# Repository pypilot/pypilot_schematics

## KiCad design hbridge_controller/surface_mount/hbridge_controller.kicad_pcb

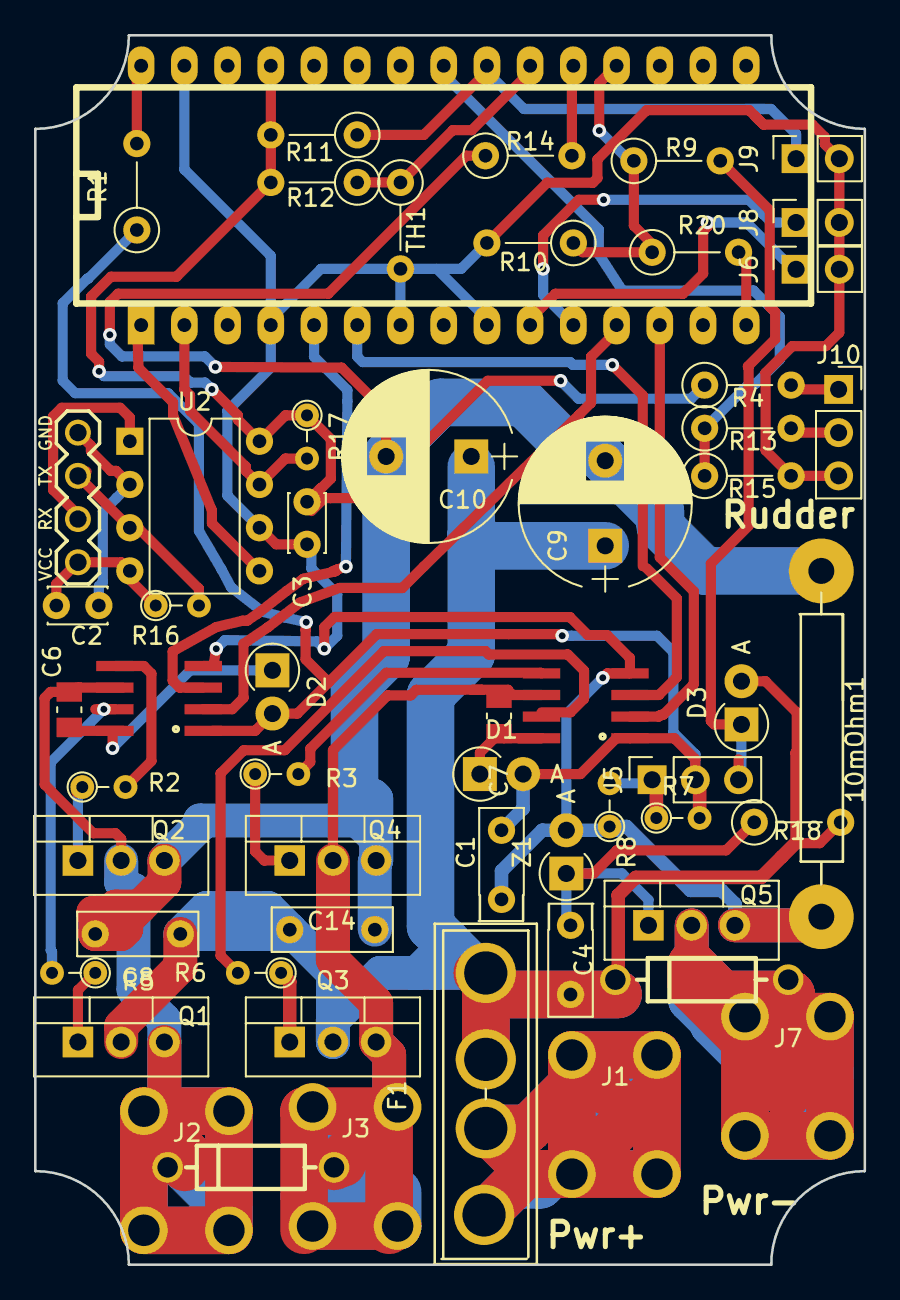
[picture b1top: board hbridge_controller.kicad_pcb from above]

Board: 2 copper layers, 48.8 x 72.2 mm, 57 parts (0 on the bottom side), 43 nets.

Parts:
10mOhm1: R; Resistor_Horizontal_RM10mm
A1: Arduino_Nano_v3.x; arduino_mini
C1, C4: 4.7uF; C_Disc_D5.0mm_W2.5mm_P2.50mm
C2, C3: .1uF; C_Disc_D3.4mm_W2.1mm_P2.50mm
C6, C7: .22uF; C_0805_2012Metric_Pad1.15x1.50mm_HandSolder
C8, C14: 4.7uF; C_Disc_D7.0mm_W2.5mm_P5.00mm
C9, C10: 330uF; CP_Radial_D10.0mm_P5.00mm
D1, D2, D3: 1N4001; D_T-1_P2.54mm_Vertical_AnodeUp
F1: FUSE; BladeFuse-CarType
J1: Pwr+; screw_terminal
J2: Motor A; screw_terminal
J3: Motor B; screw_terminal
J4: UART_Device; uart
J5: 12v REG/R; PinSocket_1x03_P2.54mm_Vertical
J6, J8, J9: Conn_01x02; PinSocket_1x02_P2.54mm_Vertical
J7: Pwr-; screw_terminal
J10: SENSE; PinSocket_1x03_P2.54mm_Vertical
Q1, Q2, Q3, Q4, Q5: Q_NMOS_GDS; TO-220-3_Vertical
R1: 100; R_Axial_DIN0207_L6.3mm_D2.5mm_P5.08mm_Vertical
R2, R3, R5, R6: 47; R_Axial_DIN0204_L3.6mm_D1.6mm_P2.54mm_Vertical
R4: 200; R_Axial_DIN0207_L6.3mm_D2.5mm_P5.08mm_Vertical
R7: 3900; R_Axial_DIN0204_L3.6mm_D1.6mm_P2.54mm_Vertical
R8: 560; R_Axial_DIN0204_L3.6mm_D1.6mm_P2.54mm_Vertical
R9, R18: 10k; R_Axial_DIN0207_L6.3mm_D2.5mm_P5.08mm_Vertical
R10, R14, R20: 560; R_Axial_DIN0207_L6.3mm_D2.5mm_P5.08mm_Vertical
R11, R12, R13: 100k; R_Axial_DIN0207_L6.3mm_D2.5mm_P5.08mm_Vertical
R15: 20k; R_Axial_DIN0207_L6.3mm_D2.5mm_P5.08mm_Vertical
R16, R17: 2.4k; R_Axial_DIN0204_L3.6mm_D1.6mm_P2.54mm_Vertical
TH1: Thermistor; R_Axial_DIN0207_L6.3mm_D2.5mm_P5.08mm_Vertical
TVS1: TVS; tvs
TVS2: TVS; DIODE-1N4001
U1, U3: NCP5106B; SO08_4mm
U2: cpc5001; DIP-8_W7.62mm
Z1: 10v; D_T-1_P2.54mm_Vertical_AnodeUp

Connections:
+5V: A1.27, C3.1, R4.1, R11.2, R12.2, R17.1, U2.8
+12V: C1.1, D1.2, D2.2, J5.2, R1.1, R7.2, U1.1, U3.1
/sense/PWMAH: A1.12, U1.2
/sense/PWMAL: A1.5, U1.3
/sense/PWMBH: A1.13, U3.2
/sense/PWMBL: A1.6, U3.3
/sense/Power: D3.1, J5.3, R9.2
/sense/Shunt: 10mOhm1.1, C8.2, C9.2, C10.2, C14.2, Q2.3, Q4.3, R14.1
GND: 10mOhm1.2, A1.4, A1.7, A1.9, A1.29, C1.2, C3.2, J6.2, J8.2, J9.2, J10.3, Q5.3, R8.1, R10.2, R15.2, TH1.2, U1.4, U2.6, U3.4, Z1.2
unnamed: A1.1, U2.5
unnamed: A1.2, R17.2, U2.7
unnamed: A1.10, J6.1
unnamed: A1.11, J8.1
unnamed: A1.15, R20.2
unnamed: A1.19, R9.1, R10.1, R20.1
unnamed: A1.20, R14.2
unnamed: A1.21, R12.1, TH1.1
unnamed: A1.22, J9.1, R11.1
unnamed: A1.23, R13.1, R15.1
unnamed: A1.30, R1.2
unnamed: C2.1, J4.1, R16.1, U2.4
unnamed: C2.2, J4.4, U2.2
unnamed: C4.2, Q5.1, R18.1, Z1.1
unnamed: C6.1, D2.1, U1.8
unnamed: C6.2, J2.1, Q1.3, Q2.2, TVS1.K, U1.6
unnamed: C7.1, D1.1, U3.8
unnamed: C7.2, J3.1, Q3.3, Q4.2, TVS1.A, U3.6
unnamed: F1.1, J1.1
unnamed: J4.2, U2.1
unnamed: J4.3, R16.2, U2.3
unnamed: J5.1, R7.1, R8.2
unnamed: J7.1, Q5.2, TVS2.A
unnamed: J10.1, R4.2
unnamed: J10.2, R13.2
unnamed: Q1.1, R5.1
unnamed: Q2.1, R2.1
unnamed: Q3.1, R6.1
unnamed: Q4.1, R3.1
unnamed: R2.2, U1.5
unnamed: R3.2, U3.5
unnamed: R5.2, U1.7
unnamed: R6.2, U3.7
VCC: C4.1, C8.1, C9.1, C10.1, C14.1, D3.2, F1.2, Q1.2, Q3.2, R18.2, TVS2.K

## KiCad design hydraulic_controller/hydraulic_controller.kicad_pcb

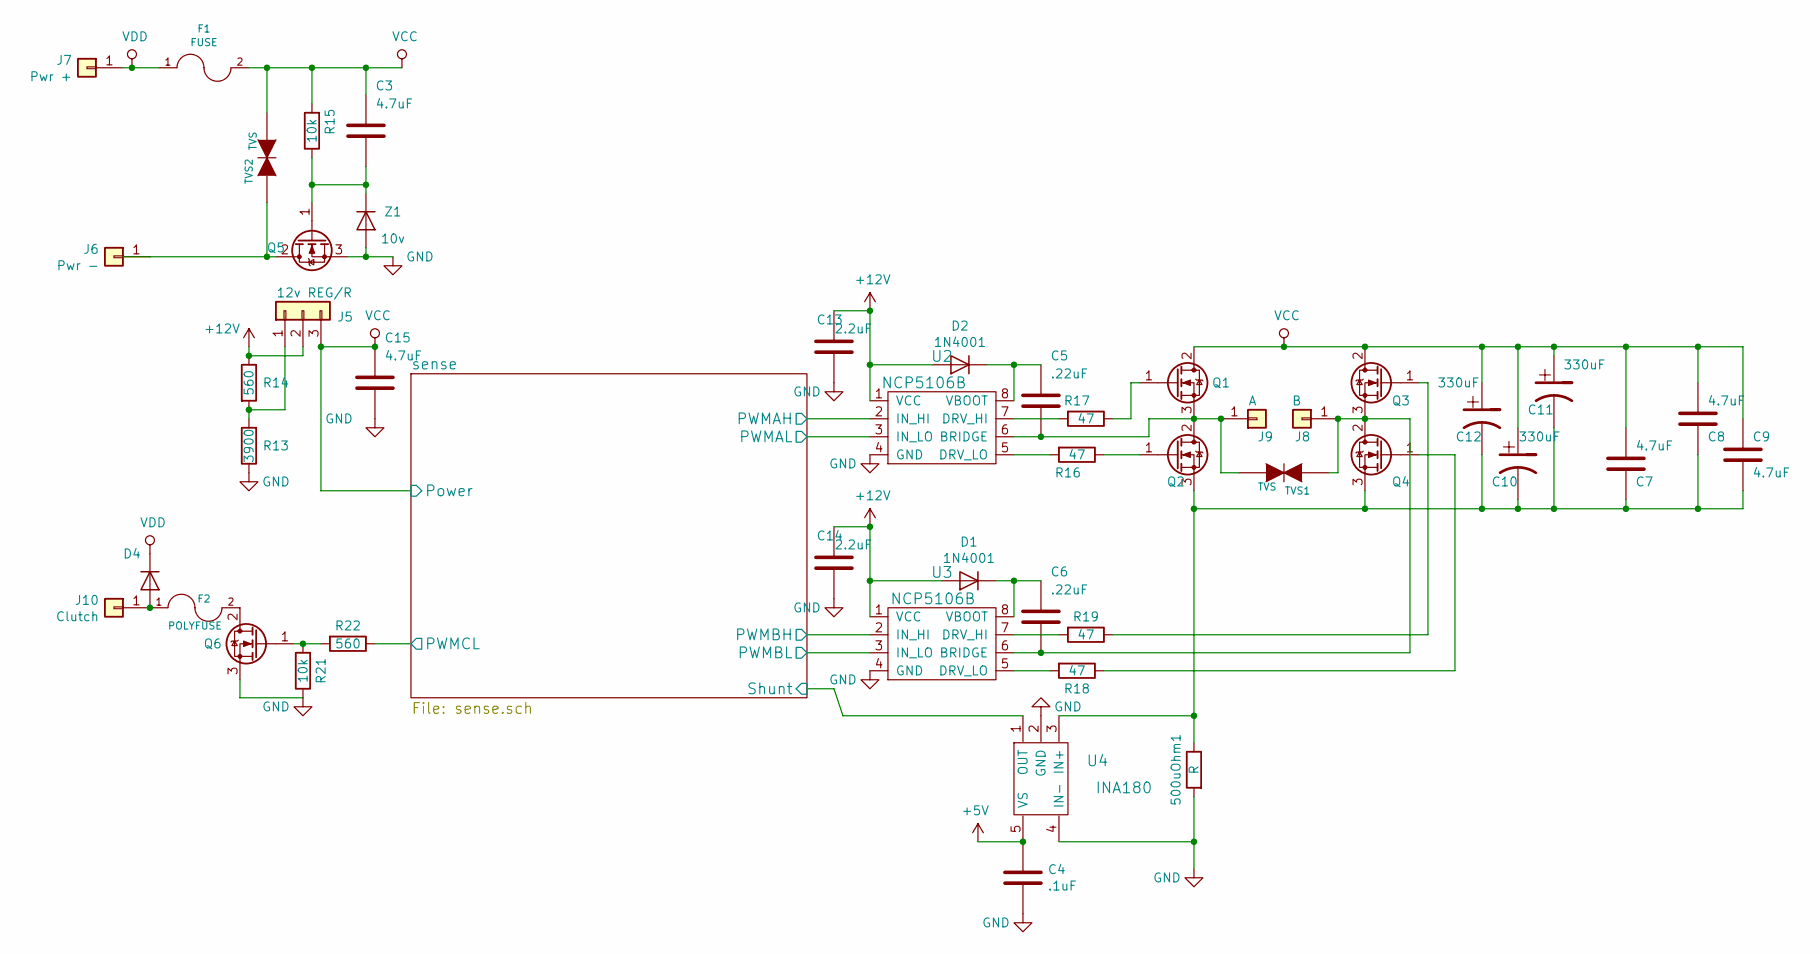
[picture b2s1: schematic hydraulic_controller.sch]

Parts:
500uOhm1: R; WSLF2512
C3, C7, C8, C9, C15: 4.7uF; C_Disc_D5.0mm_W2.5mm_P2.50mm
C4: .1uF; C_0805_2012Metric_Pad1.15x1.50mm_HandSolder
C5, C6: .22uF; C_0805_2012Metric_Pad1.15x1.50mm_HandSolder
C10, C11, C12: 330uF; CP_Radial_D16.0mm_P7.50mm
C13, C14: 2.2uF; C_1206_3216Metric_Pad1.24x1.80mm_HandSolder
D1, D2, D4: 1N4001; D_T-1_P2.54mm_Vertical_AnodeUp
F1: FUSE; MAXI FUSE CLIP
F2: POLYFUSE; R_Axial_DIN0207_L6.3mm_D2.5mm_P10.16mm_Horizontal
J5: 12v REG/R; SOT-223-3_TabPin2
J6: Pwr -; Power
J7: Pwr +; Power
J8: B; Power
J9: A; Power
J10: Clutch; Pin_d1.4mm_L8.5mm_W2.8mm_FlatFork
Q1, Q2, Q3, Q4, Q5, Q6: Q_NMOS_GDS; TO-220-3_Horizontal_nobolt
R13: 3900; R_Axial_DIN0204_L3.6mm_D1.6mm_P2.54mm_Vertical
R14: 560; R_Axial_DIN0204_L3.6mm_D1.6mm_P2.54mm_Vertical
R15, R21: 10k; R_Axial_DIN0207_L6.3mm_D2.5mm_P5.08mm_Vertical
R16, R17, R18, R19: 47; R_Axial_DIN0204_L3.6mm_D1.6mm_P5.08mm_Horizontal
R22: 560; R_Axial_DIN0207_L6.3mm_D2.5mm_P5.08mm_Vertical
TVS1: TVS; tvs
TVS2: TVS; DIODE-1N4001
U2, U3: NCP5106B; SO08_4mm
U4: INA180; SOT-23-5_HandSoldering
Z1: 10v; D_T-1_P2.54mm_Vertical_AnodeUp

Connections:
+5V: C4.1, U4.5 (VS); also elsewhere on the board
+12V: C13.1, C14.1, D1.2 (A), D2.2 (A), J5.2, R14.1, U2.1 (VCC), U3.1 (VCC); also elsewhere on the board
/sense/PWMAH: U2.2 (IN_HI); also elsewhere on the board
/sense/PWMAL: U2.3 (IN_LO); also elsewhere on the board
/sense/PWMBH: U3.2 (IN_HI); also elsewhere on the board
/sense/PWMBL: U3.3 (IN_LO); also elsewhere on the board
/sense/PWMCL: R22.1; also elsewhere on the board
/sense/Shunt: U4.1 (OUT); also elsewhere on the board
GND: 500uOhm1.2, C4.2, C13.2, C14.2, C15.2, Q5.3 (S), Q6.3 (S), R13.1, R21.1, U2.4 (GND), U3.4 (GND), U4.2 (GND), U4.4 (IN-), Z1.2 (A); also elsewhere on the board
unnamed: 500uOhm1.1, C7.2, C8.2, C9.2, C10.2 (-), C11.2 (-), C12.2 (-), Q2.3 (S), Q4.3 (S), U4.3 (IN+)
unnamed: C3.2, Q5.1 (G), R15.1, Z1.1 (K)
unnamed: C5.1, D2.1 (K), U2.8 (VBOOT)
unnamed: C5.2, J9.1, Q1.3 (S), Q2.2 (D), TVS1.K, U2.6 (BRIDGE)
unnamed: C6.1, D1.1 (K), U3.8 (VBOOT)
unnamed: C6.2, J8.1, Q3.3 (S), Q4.2 (D), TVS1.A, U3.6 (BRIDGE)
unnamed: D4.2 (A), F2.1, J10.1
unnamed: F2.2, Q6.2 (D)
unnamed: J5.1, R13.2, R14.2
unnamed: J6.1, Q5.2 (D), TVS2.A
unnamed: Q1.1 (G), R17.1
unnamed: Q2.1 (G), R16.1
unnamed: Q3.1 (G), R19.1
unnamed: Q4.1 (G), R18.1
unnamed: Q6.1 (G), R21.2, R22.2
unnamed: R16.2, U2.5 (DRV_LO)
unnamed: R17.2, U2.7 (DRV_HI)
unnamed: R18.2, U3.5 (DRV_LO)
unnamed: R19.2, U3.7 (DRV_HI)
VCC: C3.1, C7.1, C8.1, C9.1, C10.1 (+), C11.1 (+), C12.1 (+), C15.1, F1.2, J5.3, Q1.2 (D), Q3.2 (D), R15.2, TVS2.K; also elsewhere on the board
VDD: D4.1 (K), F1.1, J7.1

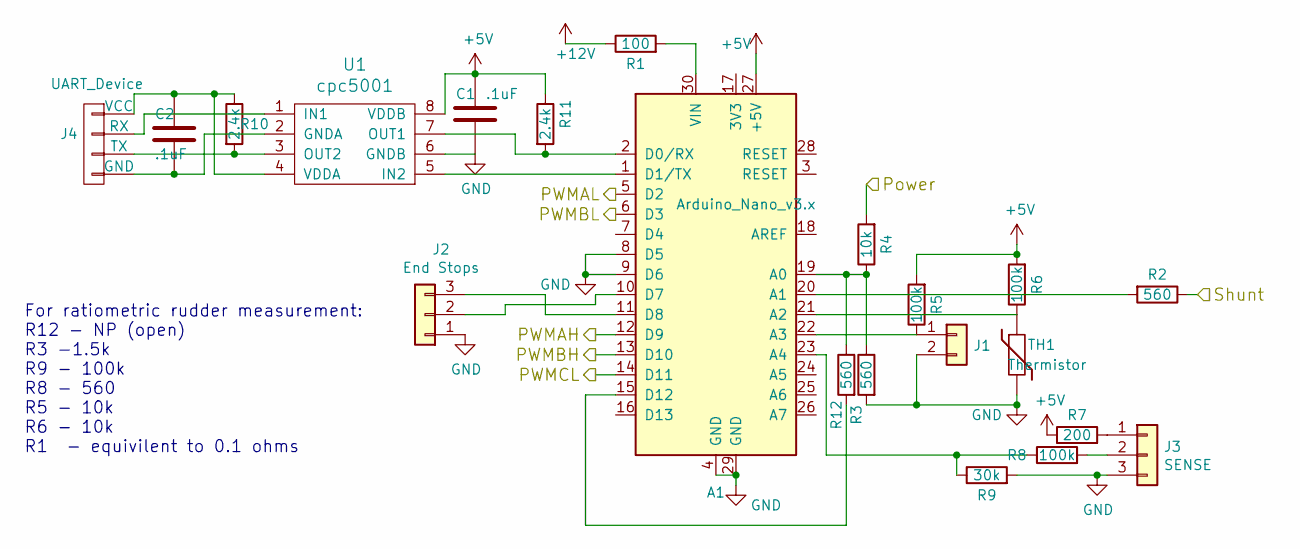
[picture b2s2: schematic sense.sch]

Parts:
A1: Arduino_Nano_v3.x; arduino_mini
C1, C2: .1uF; C_Disc_D7.0mm_W2.5mm_P5.00mm
J1: Conn_01x02; PinSocket_1x02_P2.54mm_Vertical
J2: End Stops; PinHeader_1x03_P2.54mm_Vertical
J3: SENSE; PinSocket_1x03_P2.54mm_Vertical
J4: UART_Device; uart
R1: 100; R_Axial_DIN0207_L6.3mm_D2.5mm_P10.16mm_Horizontal
R2, R3, R12: 560; R_Axial_DIN0204_L3.6mm_D1.6mm_P5.08mm_Horizontal
R4: 10k; R_Axial_DIN0204_L3.6mm_D1.6mm_P5.08mm_Horizontal
R5, R6, R8: 100k; R_Axial_DIN0204_L3.6mm_D1.6mm_P5.08mm_Horizontal
R7: 200; R_Axial_DIN0204_L3.6mm_D1.6mm_P5.08mm_Horizontal
R9: 30k; R_Axial_DIN0204_L3.6mm_D1.6mm_P5.08mm_Horizontal
R10, R11: 2.4k; R_Axial_DIN0204_L3.6mm_D1.6mm_P5.08mm_Horizontal
TH1: Thermistor; R_Axial_DIN0204_L3.6mm_D1.6mm_P5.08mm_Horizontal
U1: cpc5001; DIP-8_W7.62mm

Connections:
+5V: A1.27 (+5V), C1.1, R5.2, R6.2, R7.1, R11.1, U1.8 (VDDB); also elsewhere on the board
+12V: R1.1; also elsewhere on the board
/sense/PWMAH: A1.12 (D9); also elsewhere on the board
/sense/PWMAL: A1.5 (D2); also elsewhere on the board
/sense/PWMBH: A1.13 (D10); also elsewhere on the board
/sense/PWMBL: A1.6 (D3); also elsewhere on the board
/sense/PWMCL: A1.14 (D11); also elsewhere on the board
/sense/Shunt: R2.1; also elsewhere on the board
GND: A1.4 (GND), A1.8 (D5), A1.9 (D6), A1.29 (GND), C1.2, J1.2, J2.1, J3.3, R3.2, R9.2, TH1.2, U1.6 (GNDB); also elsewhere on the board
unnamed: A1.1 (D1/TX), U1.5 (IN2)
unnamed: A1.2 (D0/RX), R11.2, U1.7 (OUT1)
unnamed: A1.10 (D7), J2.2
unnamed: A1.11 (D8), J2.3
unnamed: A1.15 (D12), R12.2
unnamed: A1.19 (A0), R3.1, R4.1, R12.1
unnamed: A1.20 (A1), R2.2
unnamed: A1.21 (A2), R6.1, TH1.1
unnamed: A1.22 (A3), J1.1, R5.1
unnamed: A1.23 (A4), R8.1, R9.1
unnamed: A1.30 (VIN), R1.2
unnamed: C2.1, J4.1 (VCC), R10.1, U1.4 (VDDA)
unnamed: C2.2, J4.4 (GND), U1.2 (GNDA)
unnamed: J3.1, R7.2
unnamed: J3.2, R8.2
unnamed: J4.2 (RX), U1.1 (IN1)
unnamed: J4.3 (TX), R10.2, U1.3 (OUT2)
VCC: R4.2; also elsewhere on the board

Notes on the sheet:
For ratiometric rudder measurement: R12 - NP (open) R3 -1.5k R9 - 100k R8 - 560 R5 - 10k R6 - 10k R1 - equivilent to 0.1 ohms

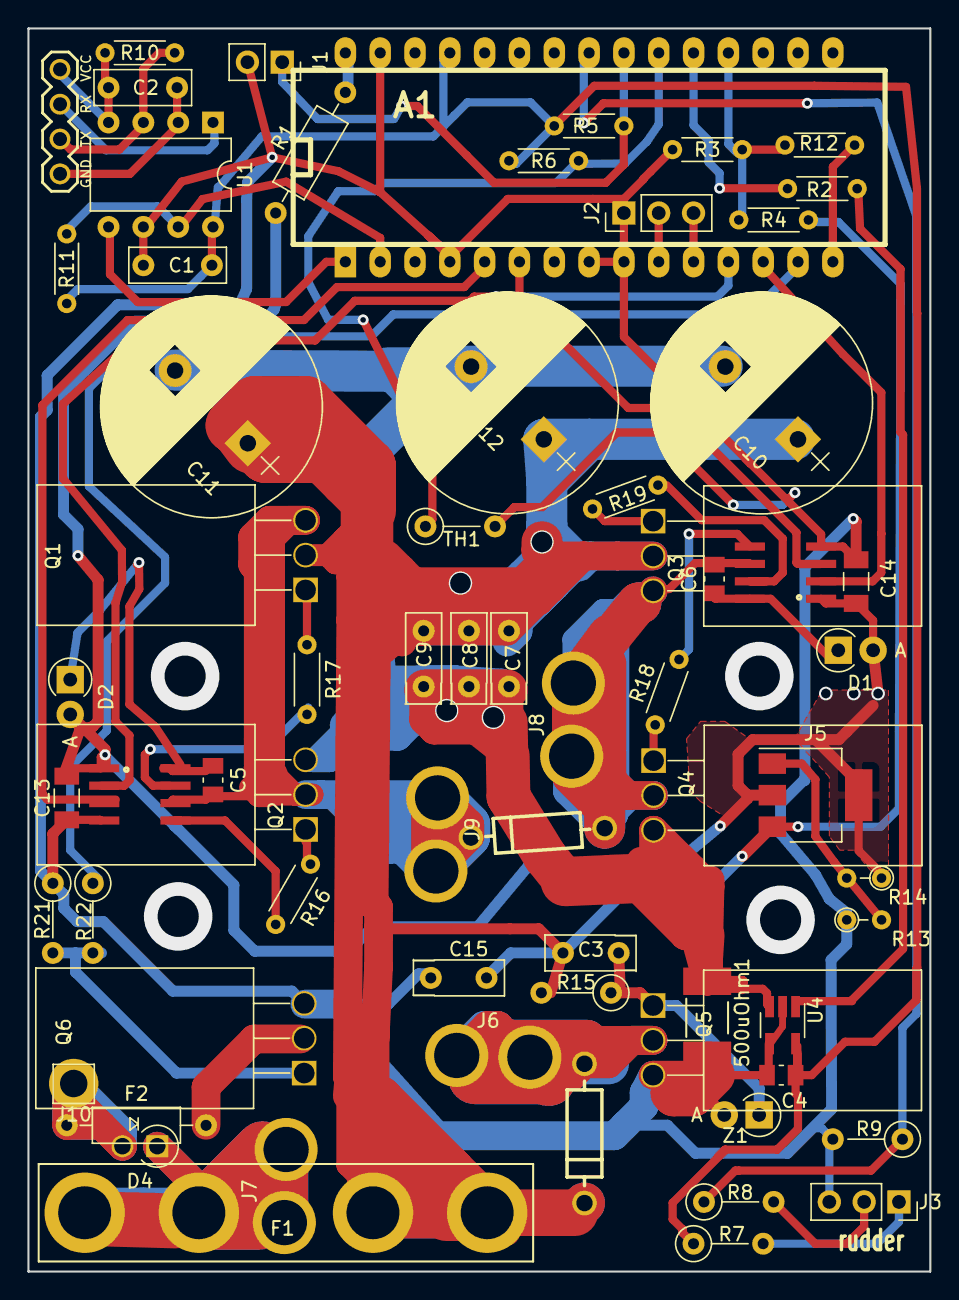
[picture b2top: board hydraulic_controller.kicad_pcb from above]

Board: 2 copper layers, 65.8 x 90.7 mm, 67 parts (0 on the bottom side), 47 nets.

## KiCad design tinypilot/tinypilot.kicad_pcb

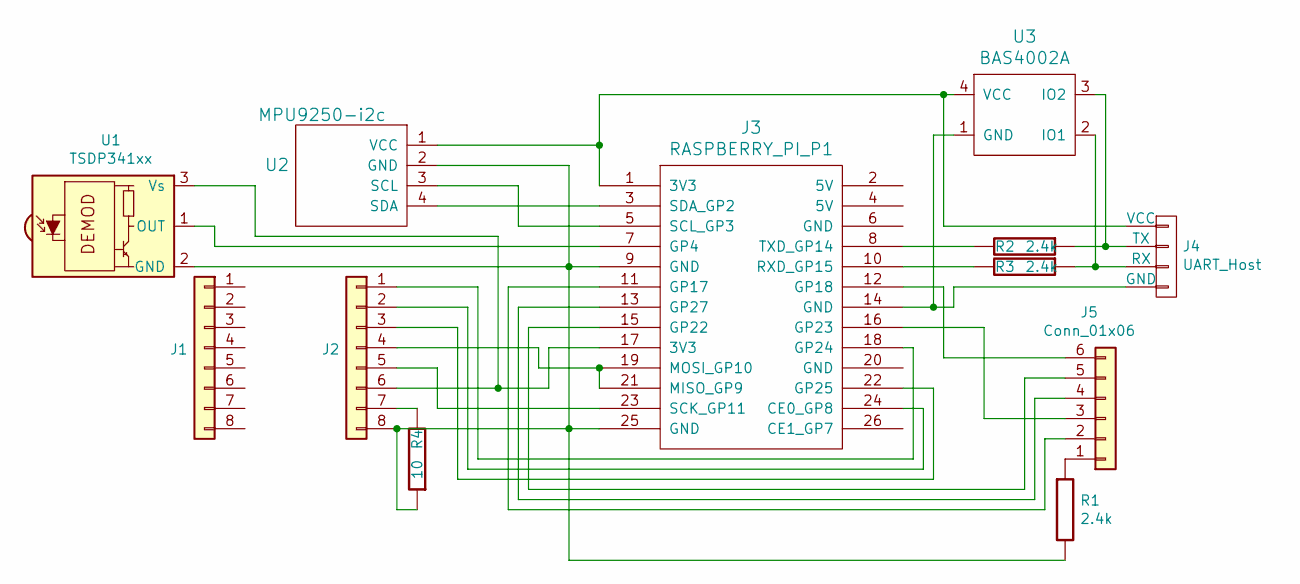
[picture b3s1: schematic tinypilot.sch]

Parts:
J1, J2: Conn_01x08; PinSocket_1x08_P2.54mm_Vertical
J3: RASPBERRY_PI_P1; 2X12
J4: UART_Host; uart_host
J5: Conn_01x06; PinSocket_1x06_P2.54mm_Vertical
R1, R2, R3: 2.4k; R_Axial_DIN0204_L3.6mm_D1.6mm_P5.08mm_Vertical
R4: 10; R_Axial_DIN0204_L3.6mm_D1.6mm_P5.08mm_Vertical
U1: TSDP341xx; IRReceiver_Vishay_MOLD-3pin
U2: MPU9250-i2c; PinSocket_1x04_P2.54mm_Vertical
U3: BAS4002A; SOT-143_Handsoldering

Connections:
unnamed: J2.1, J3.18 (GP24)
unnamed: J2.2, J3.24 (CE0_GP8)
unnamed: J2.3, J3.22 (GP25)
unnamed: J2.4, J3.19 (MOSI_GP10), J3.21 (MISO_GP9)
unnamed: J2.5, J3.23 (SCK_GP11)
unnamed: J2.6, J3.17 (3V3), U1.3 (Vs)
unnamed: J2.7, R4.2
unnamed: J2.8, J3.9 (GND), J3.25 (GND), R1.2, R4.1, U1.2 (GND), U2.2 (GND)
unnamed: J3.1 (3V3), J4.1 (VCC), U2.1 (VCC), U3.4 (VCC)
unnamed: J3.3 (SDA_GP2), U2.4 (SDA)
unnamed: J3.5 (SCL_GP3), U2.3 (SCL)
unnamed: J3.7 (GP4), U1.1 (OUT)
unnamed: J3.8 (TXD_GP14), R2.2
unnamed: J3.10 (RXD_GP15), R3.2
unnamed: J3.11 (GP17), J5.2
unnamed: J3.12 (GP18), J5.6
unnamed: J3.13 (GP27), J5.4
unnamed: J3.14 (GND), J4.4 (GND), U3.1 (GND)
unnamed: J3.15 (GP22), J5.5
unnamed: J3.16 (GP23), J5.3
unnamed: J4.2 (TX), R2.1, U3.3 (IO2)
unnamed: J4.3 (RX), R3.1, U3.2 (IO1)
unnamed: J5.1, R1.1

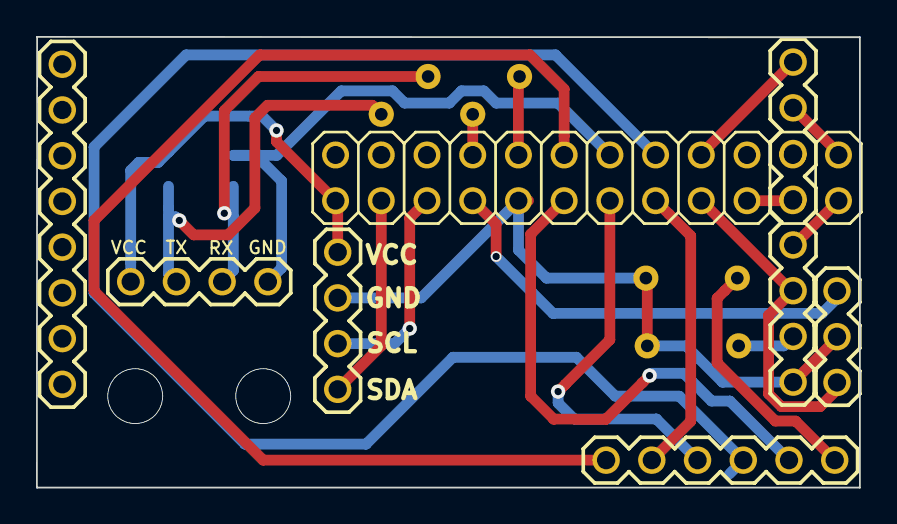
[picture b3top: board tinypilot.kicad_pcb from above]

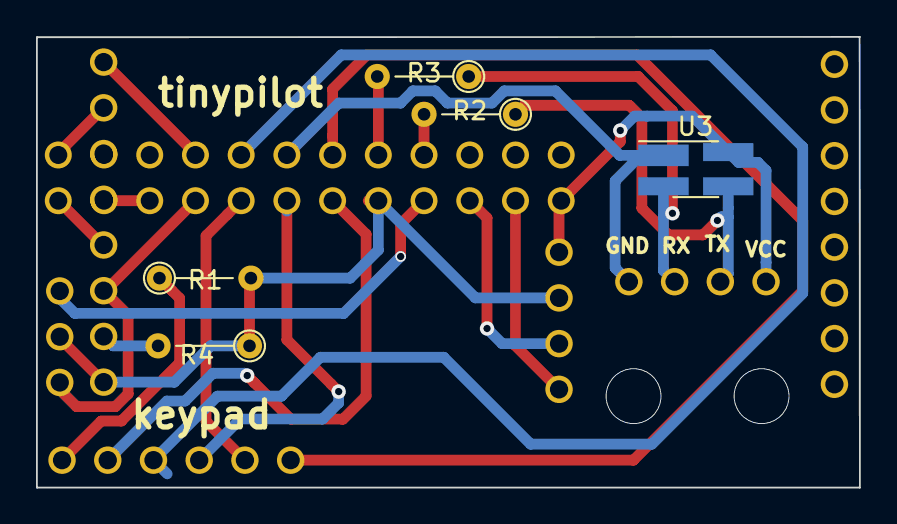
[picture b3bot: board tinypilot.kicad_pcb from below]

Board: 2 copper layers, 45.7 x 25.0 mm, 12 parts (5 on the bottom side), 23 nets.

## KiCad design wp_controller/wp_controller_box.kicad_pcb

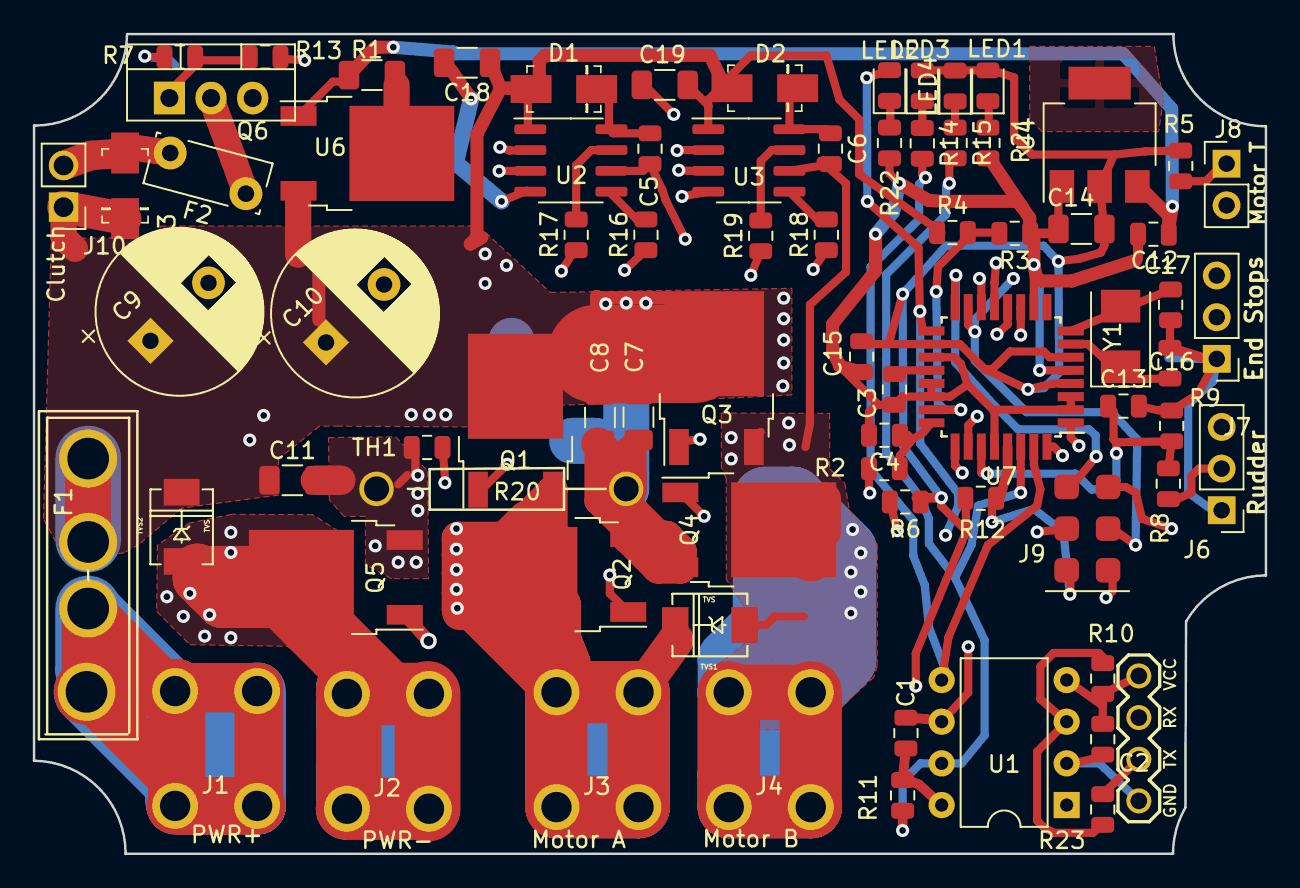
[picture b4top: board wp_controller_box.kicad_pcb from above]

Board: 4 copper layers, 75.1 x 50.0 mm, 77 parts (0 on the bottom side), 53 nets.

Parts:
C1, C2, C3, C4, C13, C15: .1uF; C_0805_2012Metric
C5, C6, C12: 1uF; C_0805_2012Metric
C7, C8, C11, C14, C18, C19: 4.7uF; C_1206_3216Metric
C9, C10: 330uF; CP_Radial_D10.0mm_P5.00mm
C16, C17: 18pF; C_0805_2012Metric
D1, D2, D3: MUR160; DO-214AC
F1: FUSE; BladeFuse-CarType
F2: Polyfuse; Fuse_Bourns_MF-RG300
J1, J3, J4: power+; screw_terminal
J2: power-; screw_terminal
J5: UART_Device; uart
J6: Rudder; PinHeader_1x03_P2.54mm_Vertical
J7: End Stops; PinHeader_1x03_P2.54mm_Vertical
J8: Conn_01x02; PinHeader_1x02_P2.54mm_Vertical
J9: ISP; PinHeader_2x03_P2.54mm_Vertical_SMD
J10: clutch; PinHeader_1x02_P2.54mm_Vertical
LED1: RED; LED_0805_2012Metric
LED2: BLUE; LED_0805_2012Metric
LED3: GREEN; LED_0805_2012Metric
LED4: YELLOW; LED_0805_2012Metric
Q1, Q2, Q3, Q4, Q5: Q_NMOS_GDS; TO-252-2
Q6: Q_NMOS_GDS; TO-220-3_Vertical
R1: 20; R_1206_3216Metric
R2, R11, R21: 2.4k; R_0805_2012Metric
R3, R13, R23: 560; R_0805_2012Metric
R4, R7, R9, R12: 10k; R_0805_2012Metric
R5, R6: 100k; R_0805_2012Metric
R8: 33k; R_0805_2012Metric
R10, R14: 2k; R_0805_2012Metric
R15, R22: 1.2k; R_0805_2012Metric
R16, R17, R18, R19: 47; R_0805_2012Metric
R20: .01; Resistor_Horizontal_RM10mm
TH1: 10k NTC; R_0805_2012Metric
TVS1, TVS2: TVS; DO-214AA
U1: cpc5001; DIP-8_W7.62mm
U2, U3: IR2101; SOIC-8_3.9x4.9mm_P1.27mm
U4: AMS1117-5.0; SOT-223-3_TabPin2
U6: LM317; TO-252-2
U7: ATmega328P-AU; TQFP-32_7x7mm_P0.8mm
Y1: 8mhz; Crystal_SMD_5032-2Pin_5.0x3.2mm

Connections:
+5V: C1.1, C14.1, C15.1, J6.3, J9.4, LED1.2, LED3.2, LED4.2, R5.1, R6.1, R11.1, R12.2, U1.8, U4.2, U7.4, U7.6, U7.18
+12V: C7.1, C8.1, C9.1, C10.1, C11.1, C18.1, C19.1, D1.2, D2.2, D3.1, F1.2, J10.1, Q1.2, Q3.2, Q5.1, R4.1, TVS2.2, U2.1, U3.1, U6.3
/sense/PWMAH: U2.2, U7.13
/sense/PWMAL: U2.3, U7.32
/sense/PWMBH: U3.2, U7.14
/sense/PWMBL: U3.3, U7.1
/sense/Shunt: C7.2, C8.2, C9.2, C10.2, Q2.3, Q4.3, R2.1, R20.1
Controller_Temp: R6.2, TH1.1, U7.25
EndA: J7.3, U7.11
EndB: J7.2, U7.12
GND: C1.2, C3.2, C4.2, C11.2, C12.2, C13.2, C14.2, C15.2, C16.1, C17.1, C18.2, C19.2, J6.1, J7.1, J8.2, J9.6, Q5.3, Q6.3, R3.1, R7.1, R9.2, R20.2, R21.2, R22.2, TH1.2, U1.6, U2.4, U3.4, U4.1, U7.2, U7.3, U7.5, U7.10, U7.19, U7.21, U7.22, U7.28
MISO: J9.1, U7.16
MOSI: J9.5, R13.1, U7.15
Motor_Temp: J8.1, R5.2, U7.26
unnamed: C2.1, J5.1, R10.1, U1.4
unnamed: C2.2, J5.4, U1.2
unnamed: C3.1, U7.20
unnamed: C4.1, R2.2, U7.24
unnamed: C5.1, D1.1, U2.8
unnamed: C5.2, J3.1, Q1.3, Q2.2, TVS1.2, U2.6
unnamed: C6.1, D2.1, U3.8
unnamed: C6.2, J4.1, Q3.3, Q4.2, TVS1.1, U3.6
unnamed: C12.1, R1.2, U4.3, U6.1
unnamed: C16.2, U7.7, Y1.1
unnamed: C17.2, U7.8, Y1.2
unnamed: D3.2, F2.2, J10.2
unnamed: F1.1, J1.1
unnamed: F2.1, Q6.2
unnamed: J2.1, Q5.2, TVS2.1
unnamed: J5.2, U1.1
unnamed: J5.3, R23.2
unnamed: J6.2, R8.2
unnamed: LED1.1, R21.1
unnamed: LED2.1, R22.1
unnamed: LED3.1, R14.1
unnamed: LED4.1, R15.1
unnamed: Q1.1, R17.1
unnamed: Q2.1, R16.1
unnamed: Q3.1, R19.1
unnamed: Q4.1, R18.1
unnamed: Q6.1, R7.2, R13.2
unnamed: R1.1, U6.2
unnamed: R10.2, R23.1, U1.3
unnamed: R16.2, U2.5
unnamed: R17.2, U2.7
unnamed: R18.2, U3.5
unnamed: R19.2, U3.7
RESET: J9.3, R12.1, U7.29
RX: R11.2, R15.2, U1.7, U7.30
Rudder: C13.1, R8.1, R9.1, U7.27
SCK: J9.2, LED2.2, U7.17
TX: R14.2, U1.5, U7.31
Voltage: R3.2, R4.2, U7.23
